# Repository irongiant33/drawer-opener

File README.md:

# Drawer Opener

## Resources

- https://lastminuteengineers.com/drv8826-stepper-motor-driver-arduino-tutorial/
- https://hackaday.io/project/183279-accelstepper-the-missing-manual/details
- https://www.airspayce.com/mikem/arduino/AccelStepper/index.html

## TODO

- What happens when something hits the drawer in the middle of movement? 
    - potentially try and measure the "fault" pin on DRV8825
    - potentially use an ultrasonic sensor to compare expected state to actual state and close the loop
- What happens when the drawer is moved when the state is "closed" or "open"?
    - potentially use an ultrasonic sensor to provide some feedback on the open loop stepper motor
- user-defined settings for speed and acceleration
- how to send commands to the system to open, close, configure, and reset?
- how to tell if the motor does not have a reasonable amount of torque to move the drawer?
    - current motor has 16N-cm of torque
- how does the system change when using an ESP32 as the main MCU rather than an arduino?

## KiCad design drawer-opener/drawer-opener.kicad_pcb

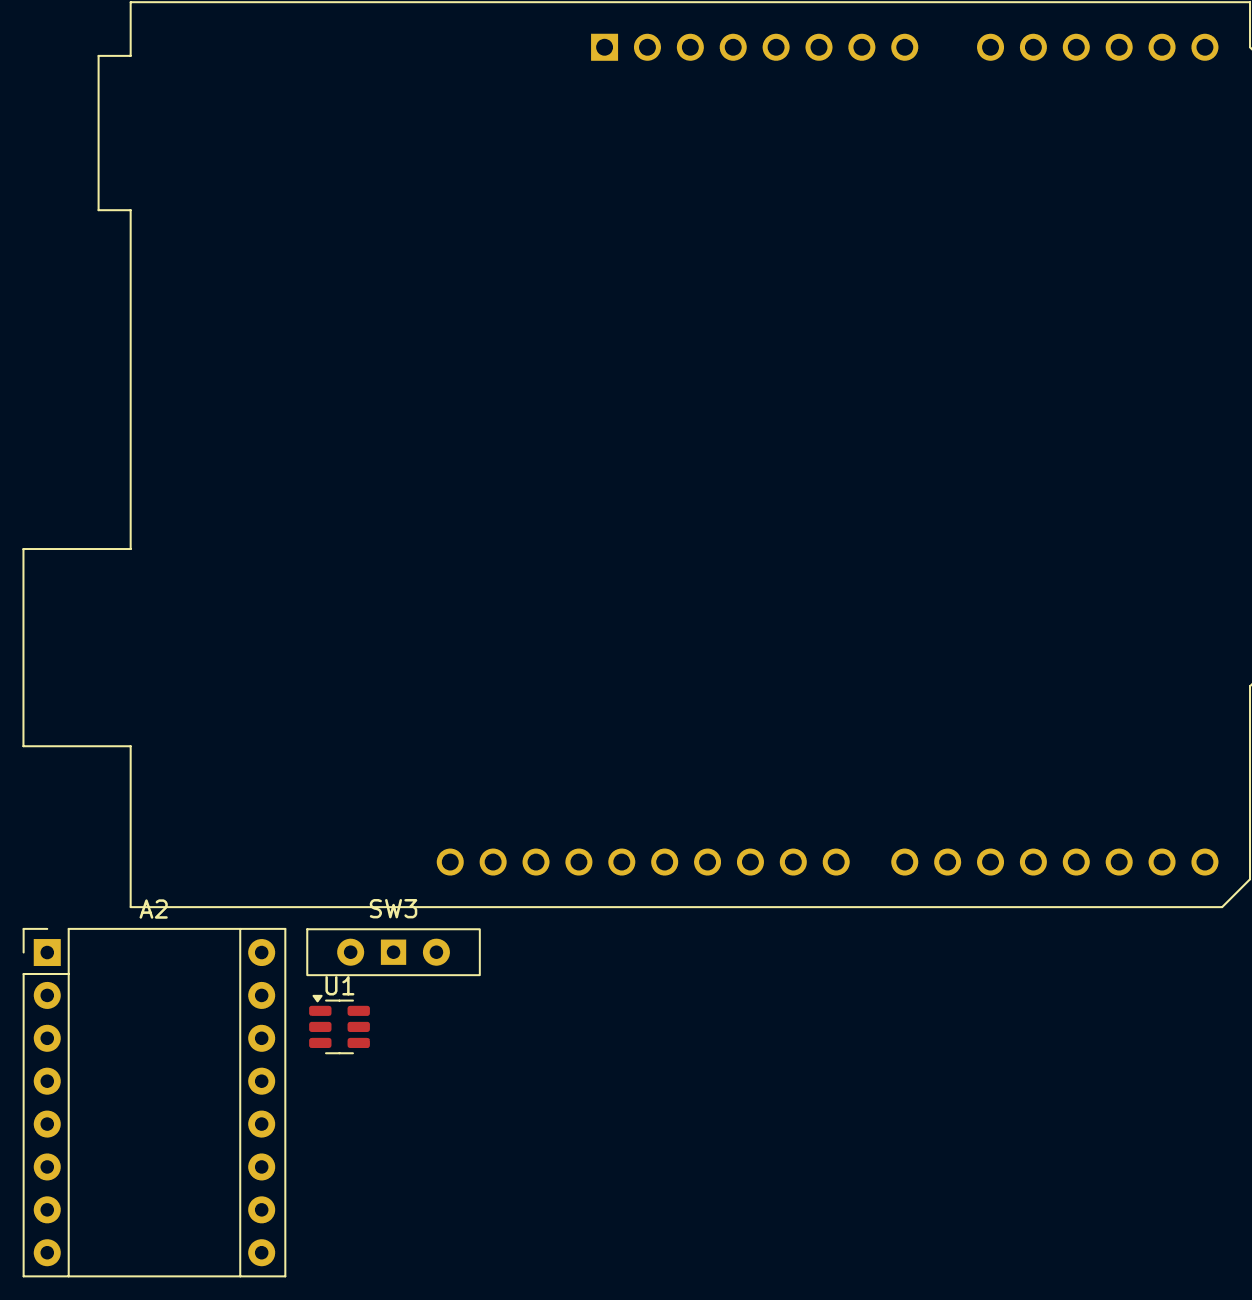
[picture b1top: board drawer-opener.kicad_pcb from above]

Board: 2 copper layers, 4 parts (0 on the bottom side), 5 nets, no tracks yet.

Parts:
A1: Arduino_UNO_R3
A2: DRV8825; Pololu_Breakout-16_15.2x20.3mm
SW3: Slide Switch; SW_Slide-03_Wuerth-WS-SLTV_10x2.5x6.4_P2.54mm
U1: MT3608; SOT-23-6

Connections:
+5V: A1.8 (VIN), A2.13 (~RST), A2.14 (~SLP), SW3.2 (C), U1.4 (EN), U1.5 (IN)
GND: A1.6 (GND), A1.7 (GND), A1.29 (GND), A2.1 (GND), A2.7 (GND), A2.10 (M0), A2.11 (M1), A2.12 (M2), SW3.3 (A), U1.2 (GND)
unnamed: A1.17 (D2), A2.16 (DIR)
unnamed: A1.18 (D3), A2.15 (STEP)
unnamed: A2.9 (~EN), SW3.1 (B)

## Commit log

2025-03-29 initial README commit
2025-03-30 initial example code for moving the carriage and for triggering limit switches
2025-03-30 stopping work for today - limit switch was not triggering in combined sketch
2025-03-30 MVP of the motor distance calibration complete. Succcessfully moves until both limit switches hit and then moves fast between the switches.
2025-04-18 saving circuit schematic, adding todos to readme, adding state machine for overall flow
